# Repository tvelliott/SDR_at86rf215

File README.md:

# SDR_at86rf215
SDR design based on the AT86RF215 transceiver with IQ LVDS / FPGA DDR (dual-data-rate) interface. The quadrature data is clocked on the rising *and* falling edges. Ethernet is 100Mbps. The firmware and HDL was written and operational in 2018. It supports stand-alone reception of P25. The firmware implementation is P25 P1 only. It does not currently do P25 P2 or P25 trunk-tracking, but the hardware is capable. It can also be used with SDR software over Ethernet such as GQRX with modified RTL-TCP drivers (mods allow 16-bit samples).

<BR>To compile:
<BR>install the gcc arm toolchain version gcc-arm-none-eabi-7-2018-q2-update/   
<BR>https://developer.arm.com/tools-and-software/open-source-software/developer-tools/gnu-toolchain/gnu-rm/downloads/7-2018-q2-update
<BR><BR>In the firmware directory, create a symbolic link to the toolchain: 
<BR>e.g.  ln -s ../gcc-arm-none-eabi-7-2018-q2-update  arm-toolchain
<BR>Then type 'make'
<BR>
<BR>
To compile the verilog code and place-route for the FPGA, you will need to install project ice-storm,Yosys, and nextpnr. In order to run the testbench for the DDR verilog code, you will also need to install iverilog and gtkwave.
<BR>
<BR>https://github.com/YosysHQ/icestorm
<BR>https://github.com/YosysHQ/yosys
<BR>https://github.com/YosysHQ/nextpnr
<BR>https://github.com/steveicarus/iverilog
<BR>https://github.com/gtkwave/gtkwave
<BR><BR>
AT86RF215 12-bit I/Q Receiver PCB / ICE40 BGA-256 FPGA / STM32H743 MCU / 100Mbps Ethernet / Stereo I2S Audio

<BR>
Dual-antenna VHF/UHF Tuner PCB (1MHz to 1200 MHz), IF output is 914 MHz and fed to the AT86RF215 receiver.
<BR>

<BR>
FPGA Routing / Usage
<BR>

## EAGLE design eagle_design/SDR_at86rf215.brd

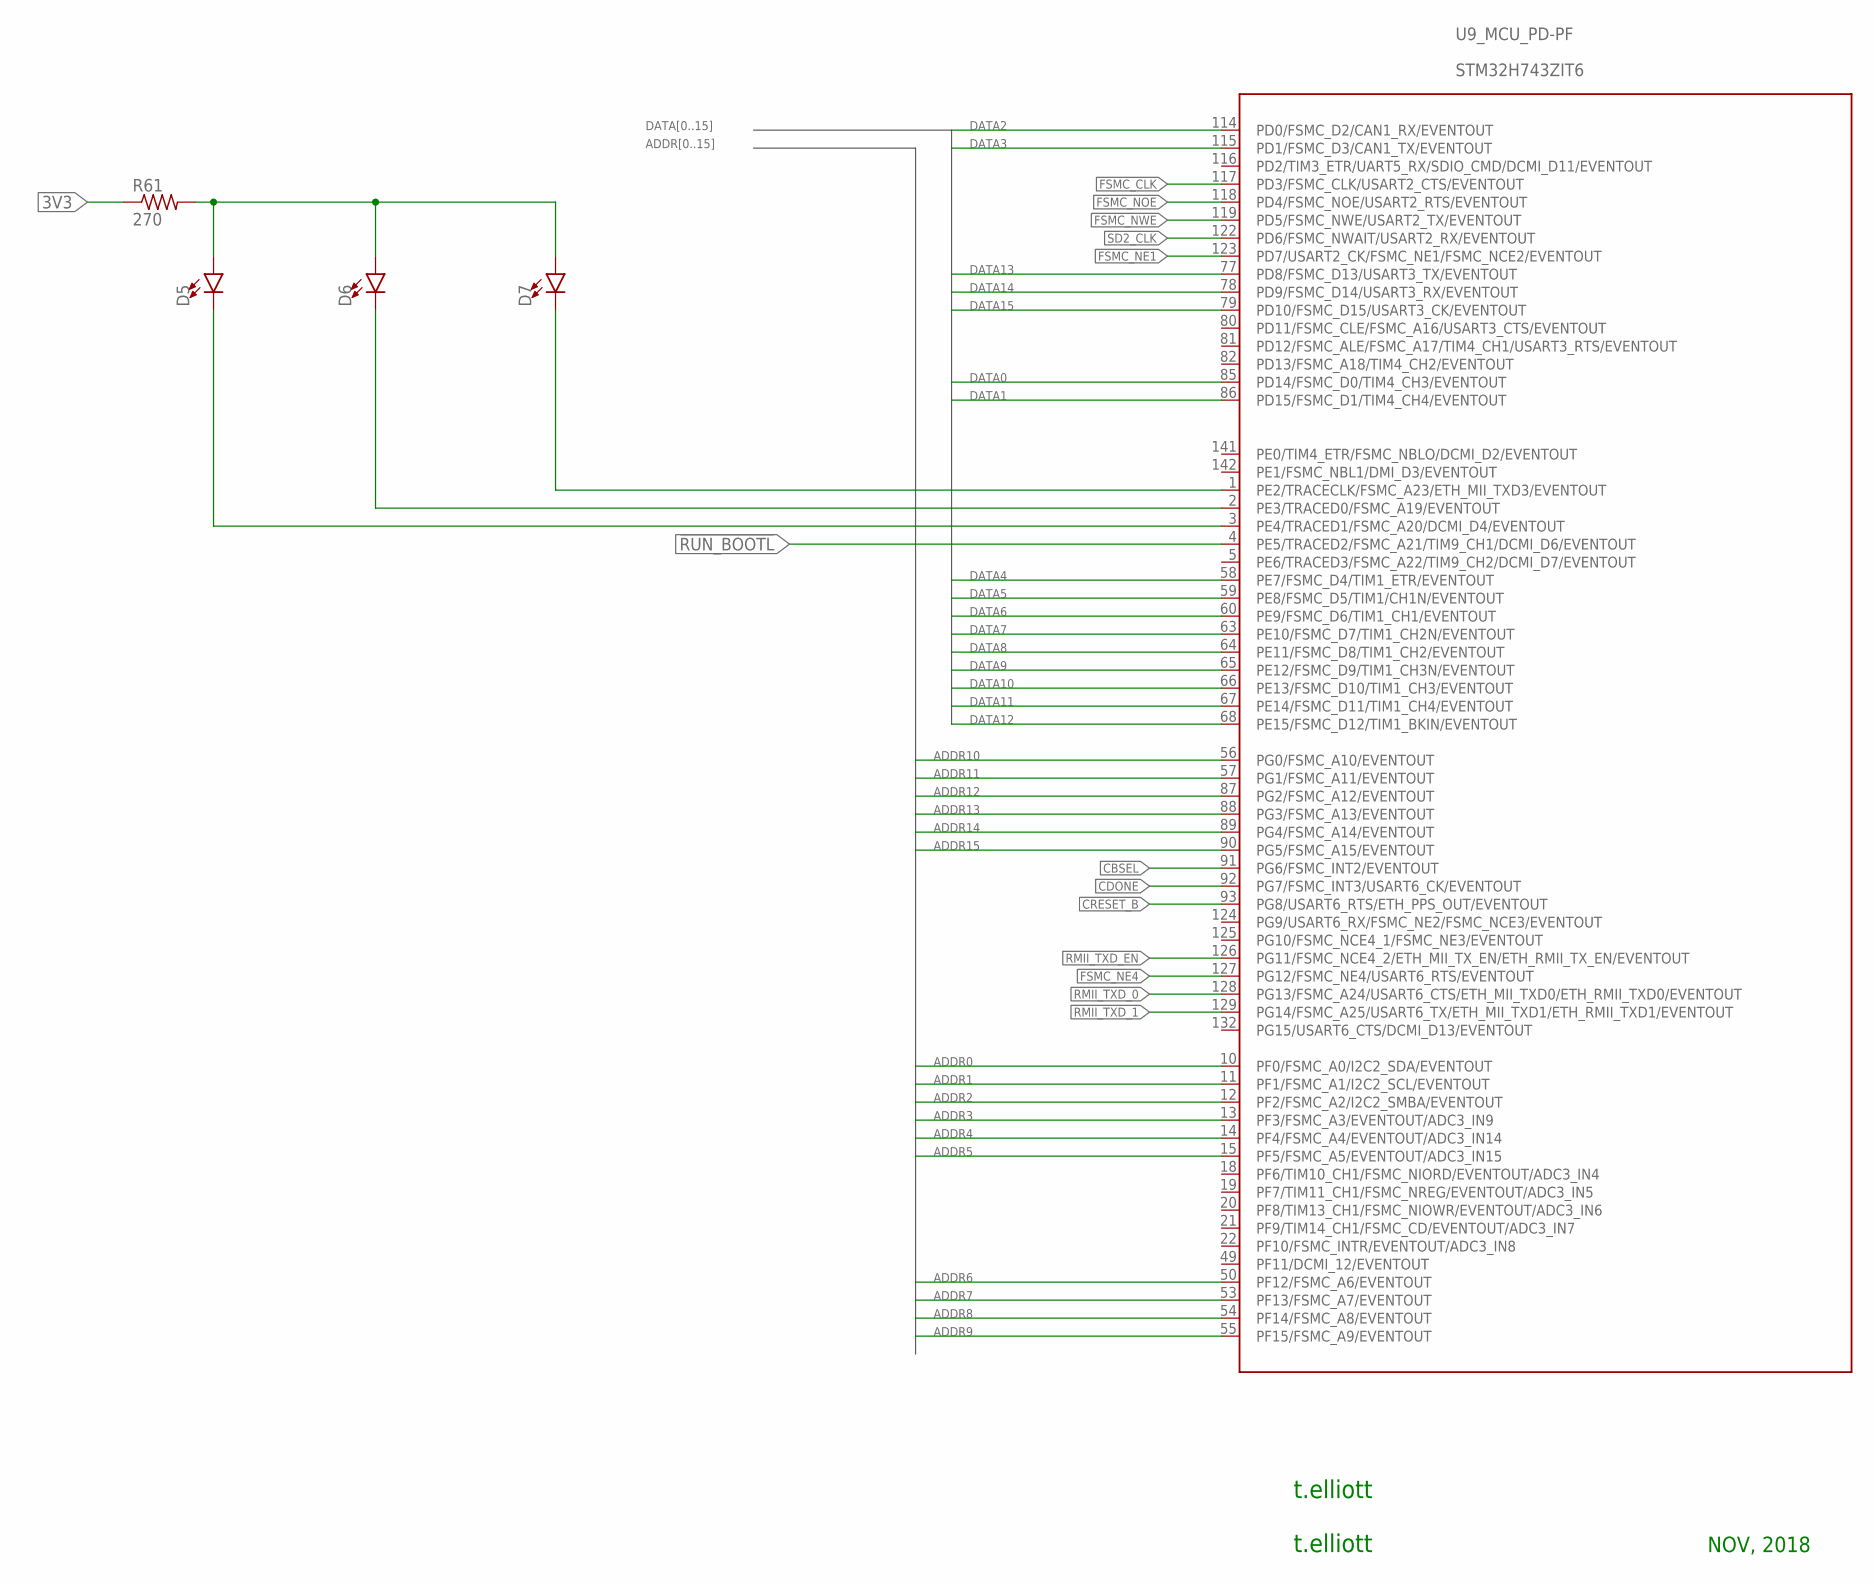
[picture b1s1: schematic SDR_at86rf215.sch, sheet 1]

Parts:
D5, D6, D7: LED1206; LED-1206
R61: 270; R0603
U9: STM32H743ZIT6; STM32F407_144

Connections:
3V3: R61.1; also elsewhere on the board
!RUN_BOOTL: U9.4 (PE5/TRACED2/FSMC_A21/TIM9_CH1/DCMI_D6/E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)
ADDR0: U9.10 (PF0/FSMC_A0/I2C2_SDA/EVENTOUT); also elsewhere on the board
ADDR1: U9.11 (PF1/FSMC_A1/I2C2_SCL/EVENTOUT); also elsewhere on the board
ADDR2: U9.12 (PF2/FSMC_A2/I2C2_SMBA/EVENTOUT); also elsewhere on the board
ADDR3: U9.13 (PF3/FSMC_A3/EVENTOUT/ADC3_IN9); also elsewhere on the board
ADDR4: U9.14 (PF4/FSMC_A4/EVENTOUT/ADC3_IN14); also elsewhere on the board
ADDR5: U9.15 (PF5/FSMC_A5/EVENTOUT/ADC3_IN15); also elsewhere on the board
ADDR6: U9.50 (PF12/FSMC_A6/EVENTOUT); also elsewhere on the board
ADDR7: U9.53 (PF13/FSMC_A7/EVENTOUT); also elsewhere on the board
ADDR8: U9.54 (PF14/FSMC_A8/EVENTOUT); also elsewhere on the board
ADDR9: U9.55 (PF15/FSMC_A9/EVENTOUT); also elsewhere on the board
ADDR10: U9.56 (PG0/FSMC_A10/EVENTOUT); also elsewhere on the board
ADDR11: U9.57 (PG1/FSMC_A11/EVENTOUT); also elsewhere on the board
ADDR12: U9.87 (PG2/FSMC_A12/EVENTOUT); also elsewhere on the board
ADDR13: U9.88 (PG3/FSMC_A13/EVENTOUT); also elsewhere on the board
ADDR14: U9.89 (PG4/FSMC_A14/EVENTOUT); also elsewhere on the board
ADDR15: U9.90 (PG5/FSMC_A15/EVENTOUT); also elsewhere on the board
CBSEL: U9.91 (PG6/FSMC_INT2/EVENTOUT); also elsewhere on the board
CDONE: U9.92 (PG7/FSMC_INT3/USART6_CK/EVENTOUT); also elsewhere on the board
CRESET_B: U9.93 (PG8/USART6_RTS/ETH_PPS_OUT/EVENTOUT); also elsewhere on the board
DATA0: U9.85 (PD14/FSMC_D0/TIM4_CH3/EVENTOUT); also elsewhere on the board
DATA1: U9.86 (PD15/FSMC_D1/TIM4_CH4/EVENTOUT); also elsewhere on the board
DATA2: U9.114 (PD0/FSMC_D2/CAN1_RX/EVENTOUT); also elsewhere on the board
DATA3: U9.115 (PD1/FSMC_D3/CAN1_TX/EVENTOUT); also elsewhere on the board
DATA4: U9.58 (PE7/FSMC_D4/TIM1_ETR/EVENTOUT); also elsewhere on the board
DATA5: U9.59 (PE8/FSMC_D5/TIM1/CH1N/EVENTOUT); also elsewhere on the board
DATA6: U9.60 (PE9/FSMC_D6/TIM1_CH1/EVENTOUT); also elsewhere on the board
DATA7: U9.63 (PE10/FSMC_D7/TIM1_CH2N/EVENTOUT); also elsewhere on the board
DATA8: U9.64 (PE11/FSMC_D8/TIM1_CH2/EVENTOUT); also elsewhere on the board
DATA9: U9.65 (PE12/FSMC_D9/TIM1_CH3N/EVENTOUT); also elsewhere on the board
DATA10: U9.66 (PE13/FSMC_D10/TIM1_CH3/EVENTOUT); also elsewhere on the board
DATA11: U9.67 (PE14/FSMC_D11/TIM1_CH4/EVENTOUT); also elsewhere on the board
DATA12: U9.68 (PE15/FSMC_D12/TIM1_BKIN/EVENTOUT); also elsewhere on the board
DATA13: U9.77 (PD8/FSMC_D13/USART3_TX/EVENTOUT); also elsewhere on the board
DATA14: U9.78 (PD9/FSMC_D14/USART3_RX/EVENTOUT); also elsewhere on the board
DATA15: U9.79 (PD10/FSMC_D15/USART3_CK/EVENTOUT); also elsewhere on the board
FSMC_CLK: U9.117 (PD3/FSMC_CLK/USART2_CTS/EVENTOUT); also elsewhere on the board
FSMC_NE1: U9.123 (PD7/USART2_CK/FSMC_NE1/FSMC_NCE2/EVENTO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); also elsewhere on the board
FSMC_NE4: U9.127 (PG12/FSMC_NE4/USART6_RTS/EVENTOUT); also elsewhere on the board
FSMC_NOE: U9.118 (PD4/FSMC_NOE/USART2_RTS/EVENTOUT); also elsewhere on the board
FSMC_NWE: U9.119 (PD5/FSMC_NWE/USART2_TX/EVENTOUT); also elsewhere on the board
unnamed: D5.A, D6.A, D7.A, R61.2
unnamed: D7.C, U9.1 (PE2/TRACECLK/FSMC_A23/ETH_MII_TXD3/EVEN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)
unnamed: D6.C, U9.2 (PE3/TRACED0/FSMC_A19/EVENTOUT)
unnamed: D5.C, U9.3 (PE4/TRACED1/FSMC_A20/DCMI_D4/EVENTOUT)
RMII_TXD_0: U9.128 (PG13/FSMC_A24/USART6_CTS/ETH_MII_TXD0/E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); also elsewhere on the board
RMII_TXD_1: U9.129 (PG14/FSMC_A25/USART6_TX/ETH_MII_TXD1/ET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); also elsewhere on the board
RMII_TXD_EN: U9.126 (PG11/FSMC_NCE4_2/ETH_MII_TX_EN/ETH_RMII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); also elsewhere on the board
SD2_CLK: U9.122 (PD6/FSMC_NWAIT/USART2_RX/EVENTOUT); also elsewhere on the board

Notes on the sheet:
t.elliott
NOV, 2018

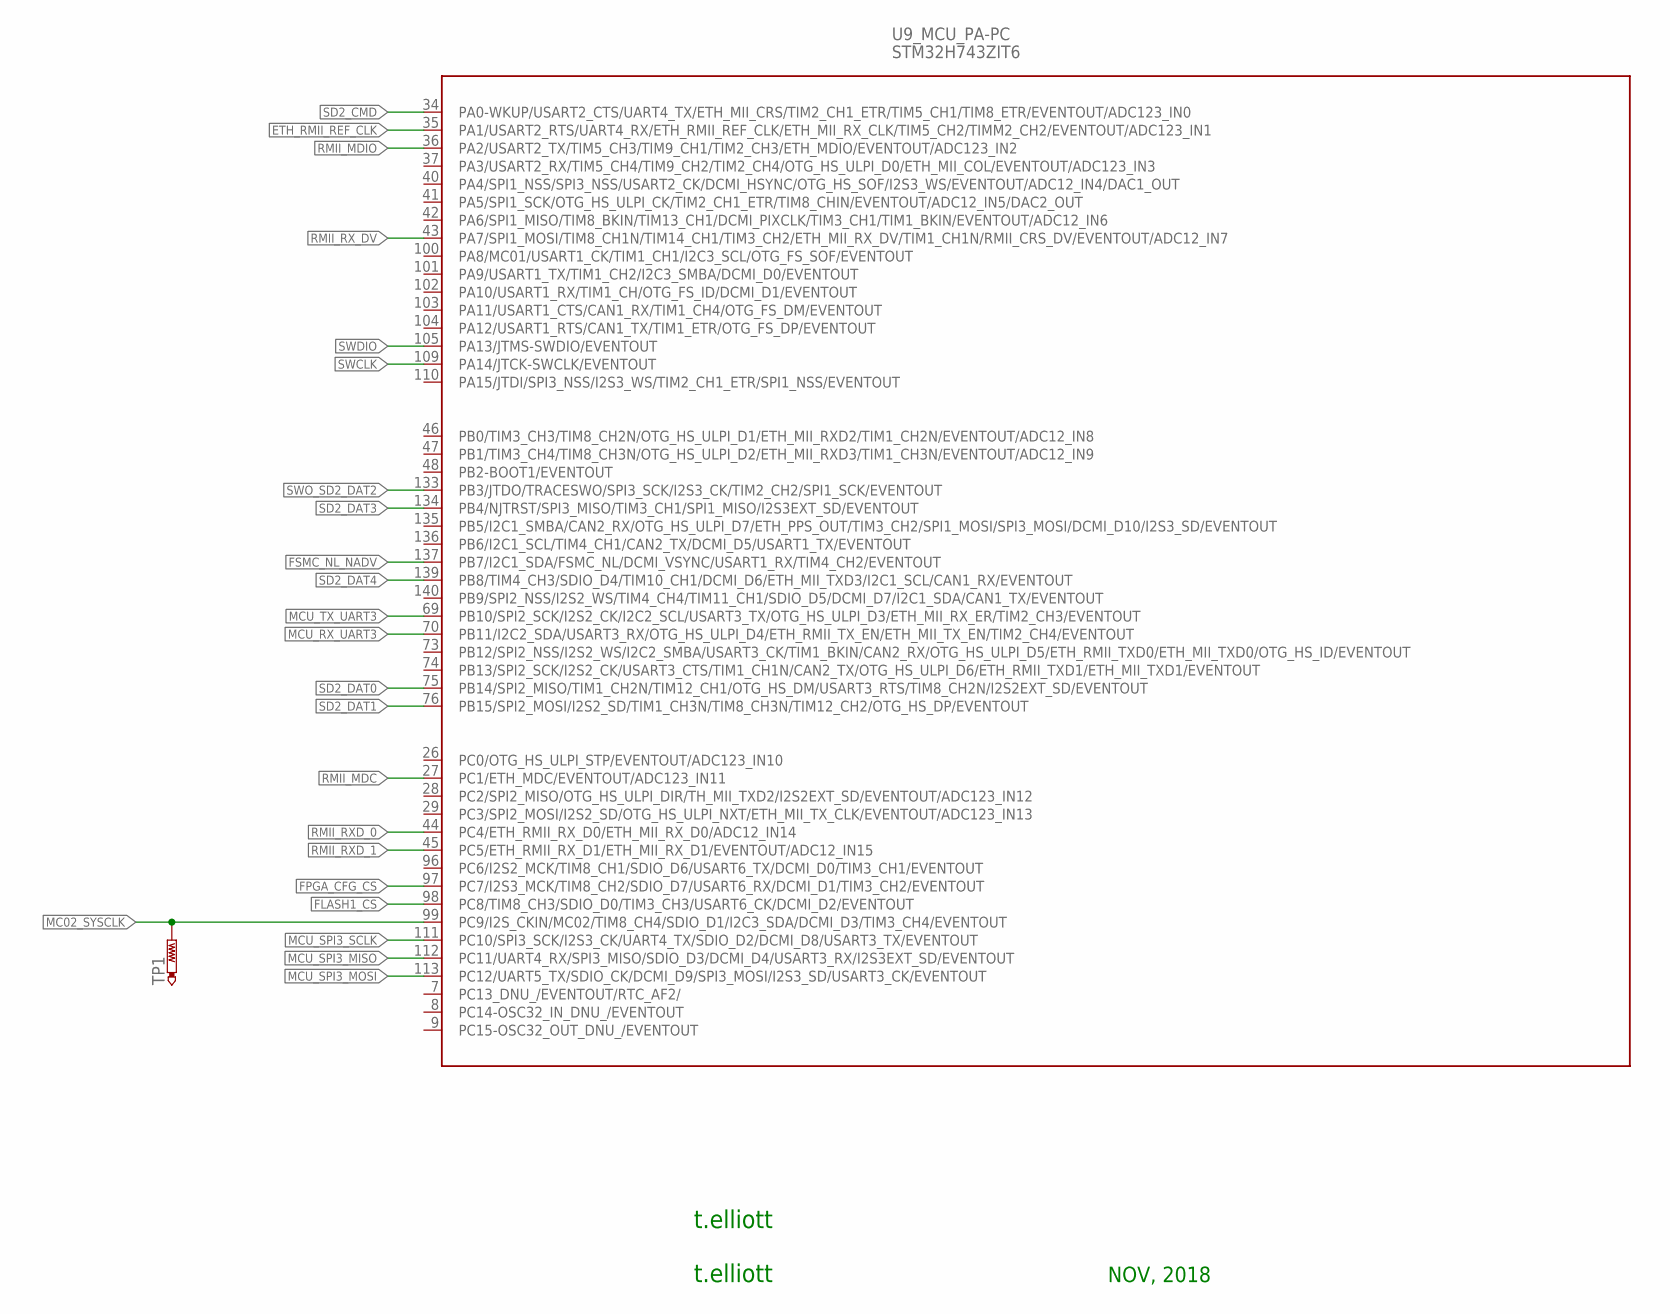
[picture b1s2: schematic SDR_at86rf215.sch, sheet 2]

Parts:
TP1: PTR1TP08R; TP08R
U9: STM32H743ZIT6; STM32F407_144

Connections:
ETH_RMII_REF_CLK: U9.35 (PA1/USART2_RTS/UART4_RX/ETH_RMII_REF_CL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); also elsewhere on the board
FLASH1_CS: U9.98 (PC8/TIM8_CH3/SDIO_D0/TIM3_CH3/USART6_CK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)
FPGA_CFG_CS: U9.97 (PC7/I2S3_MCK/TIM8_CH2/SDIO_D7/USART6_RX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); also elsewhere on the board
FSMC_NL_NADV: U9.137 (PB7/I2C1_SDA/FSMC_NL/DCMI_VSYNC/USART1_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); also elsewhere on the board
MC02_SYSCLK: TP1.TP, U9.99 (PC9/I2S_CKIN/MC02/TIM8_CH4/SDIO_D1/I2C3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); also elsewhere on the board
MCU_RX_UART3: U9.70 (PB11/I2C2_SDA/USART3_RX/OTG_HS_ULPI_D4/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); also elsewhere on the board
MCU_SPI3_MISO: U9.112 (PC11/UART4_RX/SPI3_MISO/SDIO_D3/DCMI_D4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); also elsewhere on the board
MCU_SPI3_MOSI: U9.113 (PC12/UART5_TX/SDIO_CK/DCMI_D9/SPI3_MOSI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); also elsewhere on the board
MCU_SPI3_SCLK: U9.111 (PC10/SPI3_SCK/I2S3_CK/UART4_TX/SDIO_D2/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); also elsewhere on the board
MCU_TX_UART3: U9.69 (PB10/SPI2_SCK/I2S2_CK/I2C2_SCL/USART3_T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); also elsewhere on the board
RMII_MDC: U9.27 (PC1/ETH_MDC/EVENTOUT/ADC123_IN11); also elsewhere on the board
RMII_MDIO: U9.36 (PA2/USART2_TX/TIM5_CH3/TIM9_CH1/TIM2_CH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); also elsewhere on the board
RMII_RXD_0: U9.44 (PC4/ETH_RMII_RX_D0/ETH_MII_RX_D0/ADC12_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); also elsewhere on the board
RMII_RXD_1: U9.45 (PC5/ETH_RMII_RX_D1/ETH_MII_RX_D1/EVENTO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); also elsewhere on the board
RMII_RX_DV: U9.43 (PA7/SPI1_MOSI/TIM8_CH1N/TIM14_CH1/TIM3_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); also elsewhere on the board
SD2_CMD: U9.34 (PA0-WKUP/USART2_CTS/UART4_TX/ETH_MII_CR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); also elsewhere on the board
SD2_DAT0: U9.75 (PB14/SPI2_MISO/TIM1_CH2N/TIM12_CH1/OTG_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); also elsewhere on the board
SD2_DAT1: U9.76 (PB15/SPI2_MOSI/I2S2_SD/TIM1_CH3N/TIM8_C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); also elsewhere on the board
SD2_DAT3: U9.134 (PB4/NJTRST/SPI3_MISO/TIM3_CH1/SPI1_MISO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); also elsewhere on the board
SD2_DAT4: U9.139 (PB8/TIM4_CH3/SDIO_D4/TIM10_CH1/DCMI_D6/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)
SWCLK: U9.109 (PA14/JTCK-SWCLK/EVENTOUT); also elsewhere on the board
SWDIO: U9.105 (PA13/JTMS-SWDIO/EVENTOUT); also elsewhere on the board
SWO_SD2_DAT2: U9.133 (PB3/JTDO/TRACESWO/SPI3_SCK/I2S3_CK/TIM2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); also elsewhere on the board

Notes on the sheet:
t.elliott
NOV, 2018

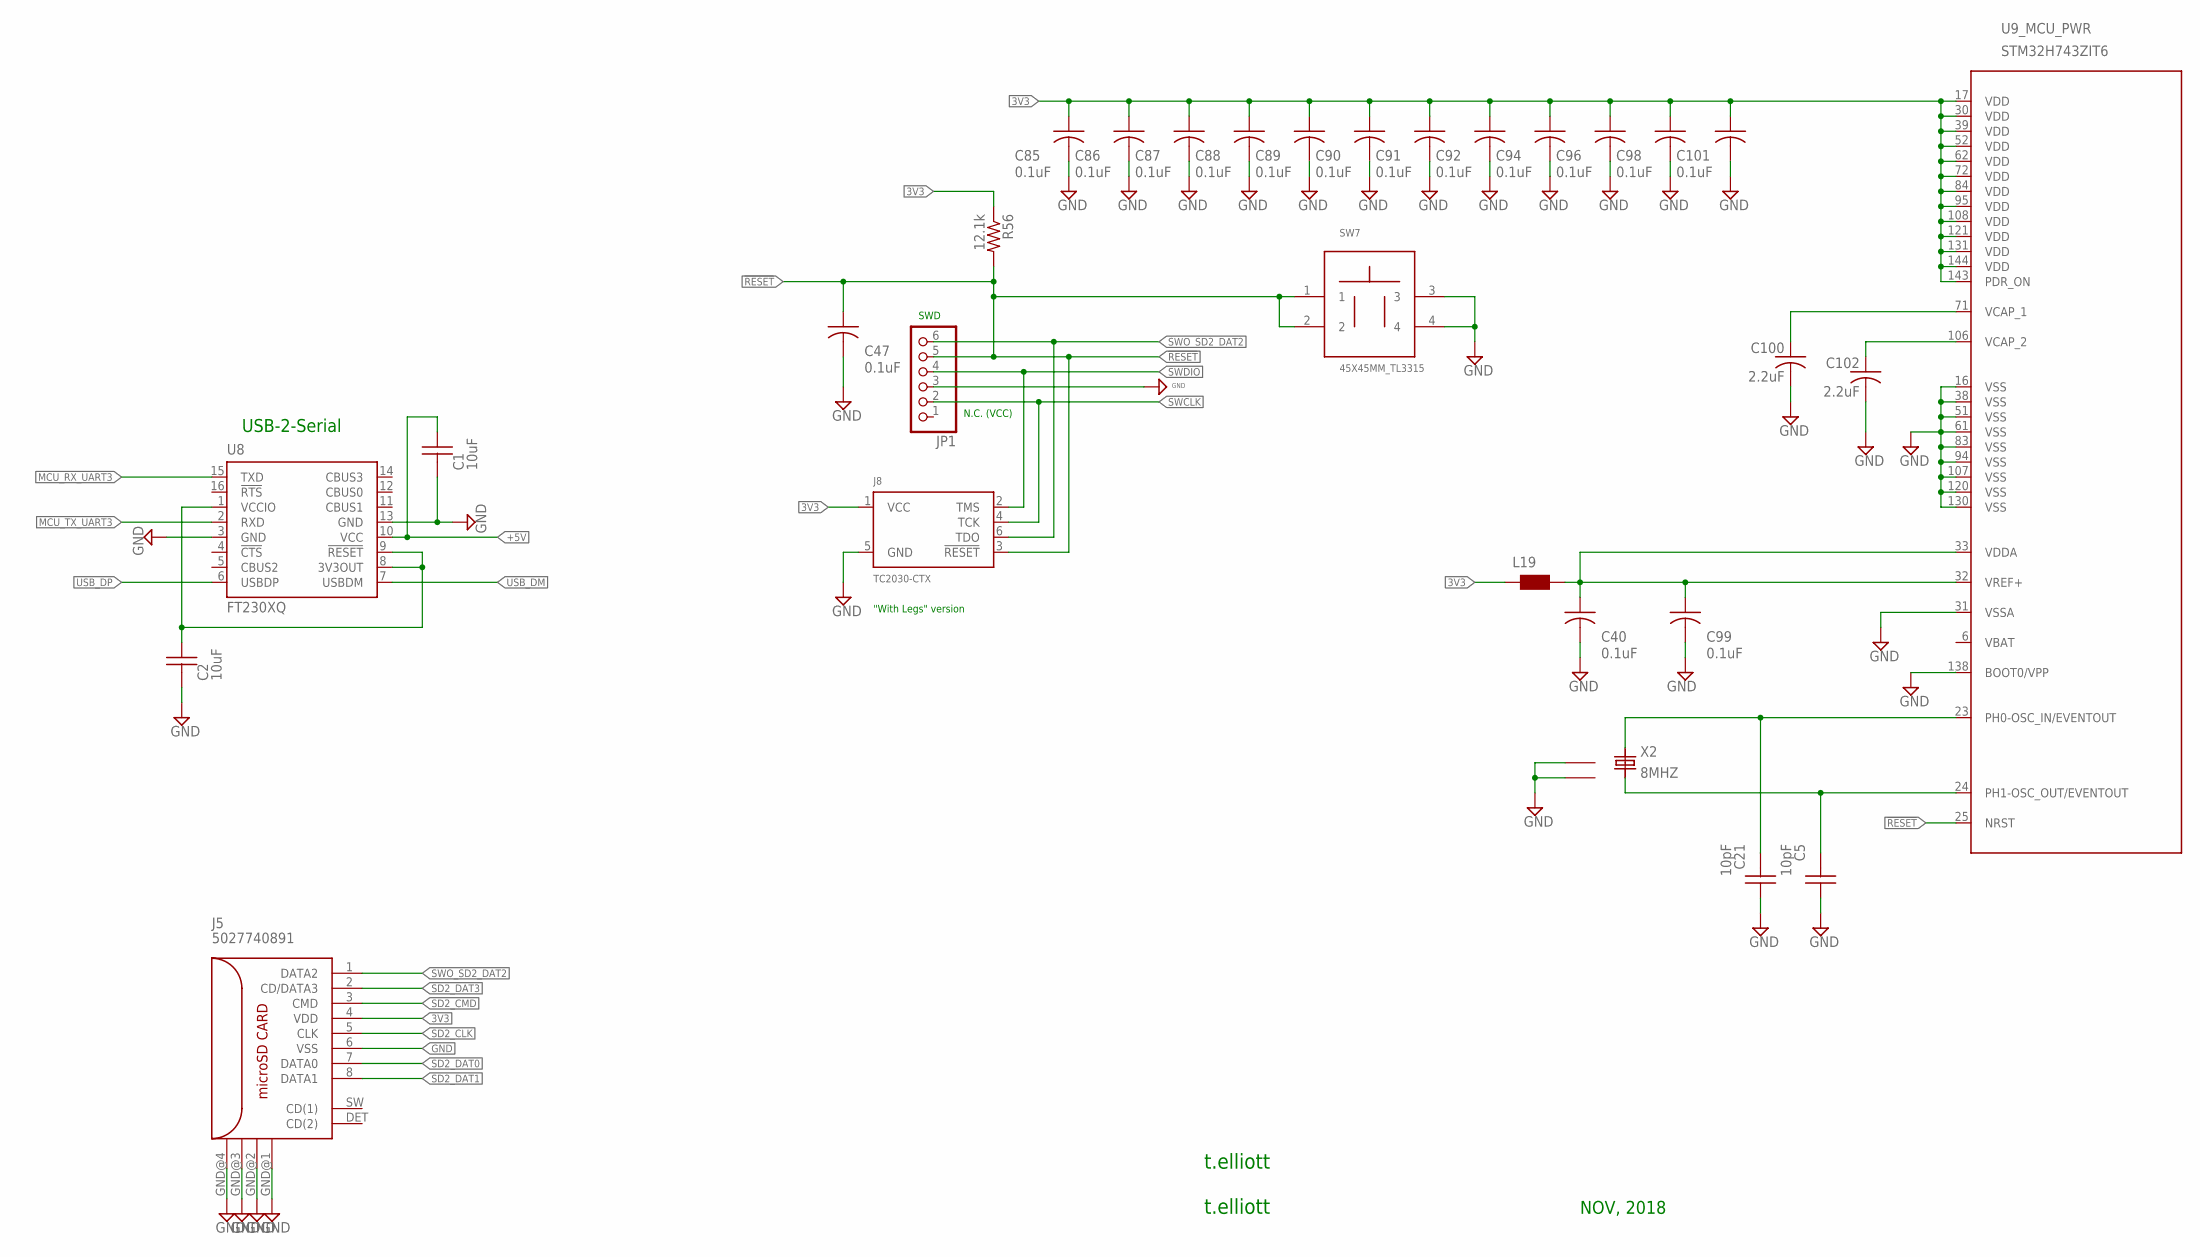
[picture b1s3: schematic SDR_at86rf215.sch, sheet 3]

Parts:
C1, C2: 10uF; C0805
C5, C21: 10pF; C0402
C40, C47, C85, C86, C87, C88, C89, C90, C91, C92, C94, C96, C98, C99, C101: 0.1uF; 0402
C100, C102: 2.2uF; C0805
J5: 5027740891; SD-502774-001
J8: TC2030-CTX; TC2030-IDC
JP1: PINHD-1X6; 1X06
L19: WE-CBF_0603; 0603
R56: 12.1k; R0603
SW7: 45X45MM_TL3315; PBUT_SW_TACTILE_4_5MMX4_5MM
U8: FT230XQ; QFN16
U9: STM32H743ZIT6; STM32F407_144
X2: 8MHZ; ECS-250-20-30B-DU_CRYSTAL

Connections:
3V3: C85.1 (A), C86.1 (A), C87.1 (A), C88.1 (A), C89.1 (A), C90.1 (A), C91.1 (A), C92.1 (A), C94.1 (A), C96.1 (A), C98.1 (A), C101.1 (A), J5.4 (VDD), J8.1 (VCC), L19.1, R56.1, U9.17 (VDD), U9.30 (VDD), U9.39 (VDD), U9.52 (VDD), U9.62 (VDD), U9.72 (VDD), U9.84 (VDD), U9.95 (VDD), U9.108 (VDD), U9.121 (VDD), U9.131 (VDD), U9.143 (PDR_ON), U9.144 (VDD); also elsewhere on the board
3V_ANALOG: C40.1 (A), C99.1 (A), L19.2, U9.32 (VREF+), U9.33 (VDDA)
20MHZ_REF: C21.2, U9.23 (PH0-OSC_IN/EVENTOUT), X2.1
!RESET: C47.1 (A), J8.3 (!RESET), JP1.5, R56.2, SW7.1, SW7.2, U9.25 (NRST); also elsewhere on the board
+5V: C1.1, U8.10 (VCC); also elsewhere on the board
GND: C1.2, C2.2, C5.1, C21.1, C40.2 (C), C47.2 (C), C85.2 (C), C86.2 (C), C87.2 (C), C88.2 (C), C89.2 (C), C90.2 (C), C91.2 (C), C92.2 (C), C94.2 (C), C96.2 (C), C98.2 (C), C99.2 (C), C100.2, C101.2 (C), C102.2, J5.6 (VSS), J5.GND@1 (GND), J5.GND@2 (GND), J5.GND@3 (GND), J5.GND@4 (GND), J8.5 (GND), JP1.3, SW7.3, SW7.4, U8.3 (GND), U8.13 (GND), U9.16 (VSS), U9.31 (VSSA), U9.38 (VSS), U9.51 (VSS), U9.61 (VSS), U9.83 (VSS), U9.94 (VSS), U9.107 (VSS), U9.120 (VSS), U9.130 (VSS), U9.138 (BOOT0/VPP), X2.GND@1 (1), X2.GND@2 (2); also elsewhere on the board
MCU_RX_UART3: U8.15 (TXD); also elsewhere on the board
MCU_TX_UART3: U8.2 (RXD); also elsewhere on the board
unnamed: C102.1, U9.106 (VCAP_2)
unnamed: C2.1, U8.1 (VCCIO), U8.8 (3V3OUT), U8.9 (!RESET)
unnamed: C100.1, U9.71 (VCAP_1)
SD2_CLK: J5.5 (CLK); also elsewhere on the board
SD2_CMD: J5.3 (CMD); also elsewhere on the board
SD2_DAT0: J5.7 (DATA0); also elsewhere on the board
SD2_DAT1: J5.8 (DATA1); also elsewhere on the board
SD2_DAT3: J5.2 (CD/DATA3); also elsewhere on the board
SWCLK: J8.4 (TCK), JP1.2; also elsewhere on the board
SWDIO: J8.2 (TMS), JP1.4; also elsewhere on the board
SWO_SD2_DAT2: J5.1 (DATA2), J8.6 (TDO), JP1.6; also elsewhere on the board
USB_DM: U8.7 (USBDM); also elsewhere on the board
USB_DP: U8.6 (USBDP); also elsewhere on the board
X2: C5.2, U9.24 (PH1-OSC_OUT/EVENTOUT), X2.3

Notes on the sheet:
t.elliott
SWD
USB-2-Serial
N.C. (VCC)
"With Legs" version
NOV, 2018

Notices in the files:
parts and their libraries:
cirrus-3: Copyright (C) 2005 by Bob Starr, rtzaudio@mindspring.com
SparkFun-LED: Licensing: Creative Commons ShareAlike 4.0 International - https://creativecommons.org/licenses/by-sa/4.0
